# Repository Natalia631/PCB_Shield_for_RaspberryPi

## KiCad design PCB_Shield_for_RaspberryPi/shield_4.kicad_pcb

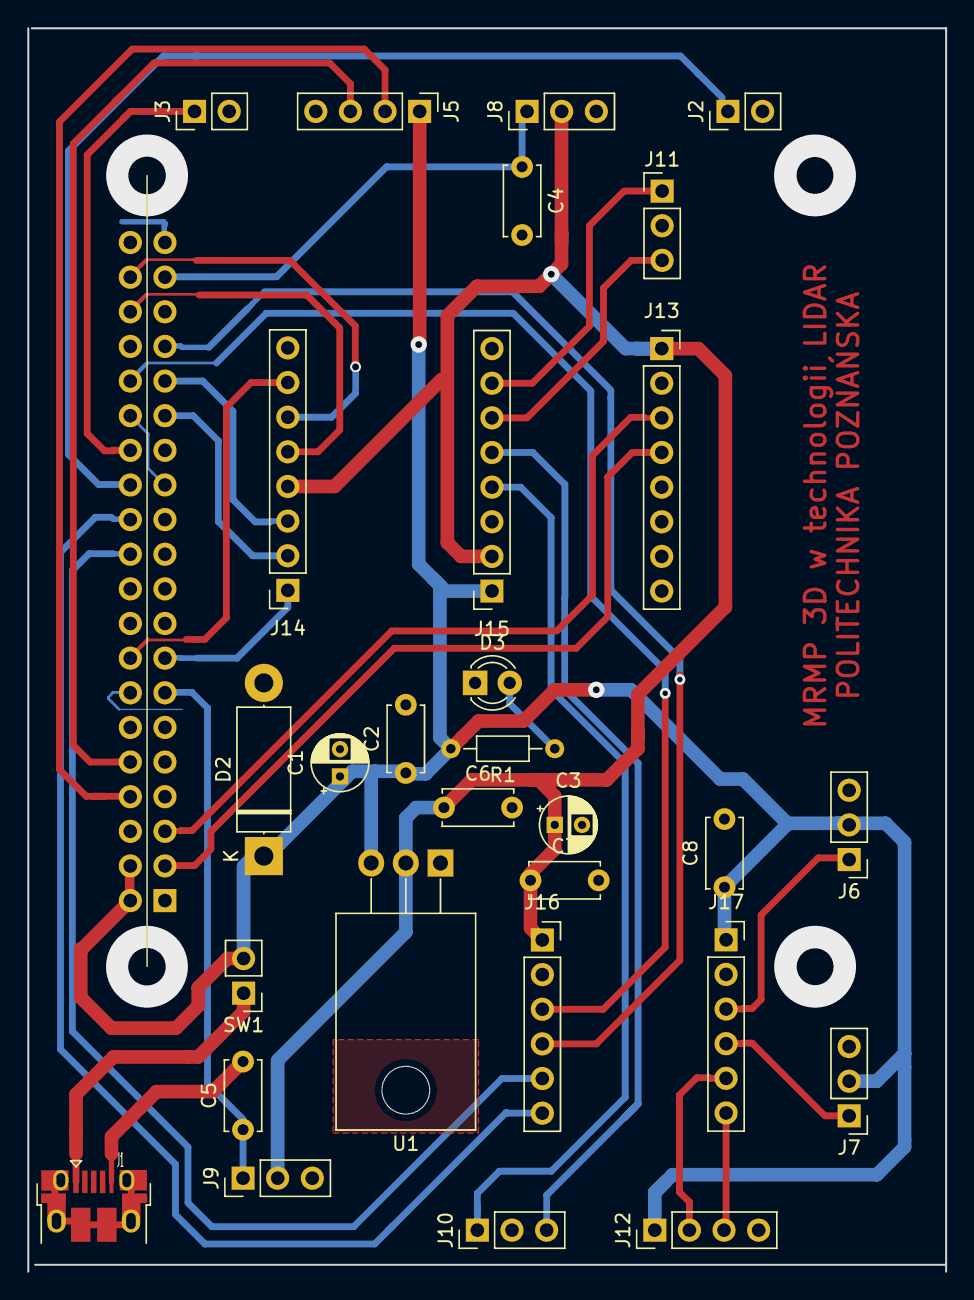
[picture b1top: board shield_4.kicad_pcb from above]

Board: 2 copper layers, 67.3 x 91.2 mm, 30 parts (1 on the bottom side), 31 nets.

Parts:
C1: 470u; CP_Radial_D4.0mm_P2.00mm
C2: 100n; C_Disc_D4.7mm_W2.5mm_P5.00mm
C3: 100u; CP_Radial_D4.0mm_P2.00mm
C4, C5, C6, C7, C8: 100n; C_Disc_D5.0mm_W2.5mm_P5.00mm
D2: 1N5822; D_5W_P12.70mm_Horizontal
D3: GREEN ON; LED_D3.0mm
J1: USB_B_Micro; USB_Micro-B_Amphenol_10103594-0001LF_Horizontal
J2: KRAN_PRZOD; PinHeader_1x02_P2.54mm_Vertical
J3: KRAN_TYL; PinHeader_1x02_P2.54mm_Vertical
J4: Raspberry_Pi_2_3; PinSocket_2x20_P2.54mm_Vertical
J5: LIDAR; PinHeader_1x04_P2.54mm_Vertical
J6: SERWO_POZIOM; PinHeader_1x03_P2.54mm_Vertical
J7: SERWO_PION; PinHeader_1x03_P2.54mm_Vertical
J8: ENKODER_PRAWY; PinHeader_1x03_P2.54mm_Vertical
J9: ENKODER_LEWY; PinHeader_1x03_P2.54mm_Vertical
J10: LEWY_SILNIK_DC; PinHeader_1x03_P2.54mm_Vertical
J11: PRAWY_SILNIK_DC; PinHeader_1x03_P2.54mm_Vertical
J12: SENSOR_ULTRA; PinHeader_1x04_P2.54mm_Vertical
J13: mpu-6050; PinSocket_1x08_P2.54mm_Vertical
J14: Mostek_HP; PinSocket_1x08_P2.54mm_Vertical
J15: Mostek_HL; PinSocket_1x08_P2.54mm_Vertical
J16: Tłumacz_L; PinSocket_1x06_P2.54mm_Vertical
J17: Tłumacz_P; PinSocket_1x06_P2.54mm_Vertical
R1: 1K; R_Axial_DIN0204_L3.6mm_D1.6mm_P7.62mm_Horizontal
SW1: SW_SPST; PinHeader_1x02_P2.54mm_Vertical
U1: AZ1117-3.3; TO-220-3_Horizontal_TabDown

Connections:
+3V3: C3.1, C6.1, C7.1, J8.2, J9.2, J13.1, J14.4, J15.2, J16.1, U1.2
+5V: C1.1, C2.1, C8.1, D2.1, J4.2, J4.4, J5.1, J6.2, J7.2, J12.1, J15.1, J17.1, R1.2, SW1.2, U1.3
/ECHO_SEN: J12.3, J17.6
/ECHO_TL: J4.24, J16.6
/EN_LEWY: C5.1, J4.13, J9.1
/EN_PRAWY: C4.1, J4.37, J8.1
/KRAN_PRZOD: J2.1, J4.26
/KRAN_TYL: J3.1, J4.28
/L_DC_M_H1: J4.29, J14.2
/L_DC_M_H2: J4.31, J14.3
/L_DC_SILNIK1: J10.1, J15.4
/L_DC_SILNIK2: J10.3, J15.5
/L_RX: J4.8, J5.2
/L_TX: J4.10, J5.3
/PWM_DC_M_H_A: J4.15, J14.1
/PWM_DC_M_H_B: J4.16, J14.7
/PWM_PIO_SER: J7.1, J17.4
/PWM_PIO_TL: J4.33, J16.4
/PWM_POZ_SER: J6.1, J17.3
/PWM_POZ_TL: J4.32, J16.3
/P_DC_M_H1: J4.36, J14.5
/P_DC_M_H2: J4.38, J14.6
/P_DC_SILNIK1: J11.1, J15.7
/P_DC_SILNIK2: J11.3, J15.6
/SCL_I2C: J4.5, J13.3
/SDA_I2C: J4.3, J13.4
/TRIG_SEN: J12.2, J17.5
/TRIG_TL: J4.22, J16.5
GND: C1.2, C2.2, C3.2, C4.2, C5.2, C6.2, C7.2, C8.2, D2.2, D3.1, J1.5, J2.2, J3.2, J4.6, J4.9, J4.14, J4.20, J4.25, J4.30, J4.34, J4.39, J5.4, J6.3, J7.3, J8.3, J9.3, J12.4, J13.2, J14.8, J15.3, J15.8, J16.2, J17.2, U1.1
unnamed: D3.2, R1.1
unnamed: J1.1, SW1.1

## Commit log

2020-02-14 Add files via upload
    Designed shield in the form of a printed circuit board for Raspberry PI 3B +, which was used in the construction of a mobile robot for 3D scanning in LIDAR technology.
    The board contains:
    • connector for the GPIO Raspberry Pi 3B + bus,
    • USB 5 V power connector,
    • voltage regulator for 3.3 V powered by 5 V,
    • connector for LIDAR sensor,
